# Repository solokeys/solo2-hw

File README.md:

# Solo v2 Hardware

This repo contains the schematic and layout for Solo v2.  Specifically, it contains the Kicad source files
for the "module" PCB which contains all of the relevant circuitry.

What is not included is the "cavity" PCBs, or NFC antenna.

To generate a BOM, see [`bom/`](./bom).

This is only provided as a reference.  If you'd like to submit a PR or otherwise provide feedback, please contact SoloKeys team first.

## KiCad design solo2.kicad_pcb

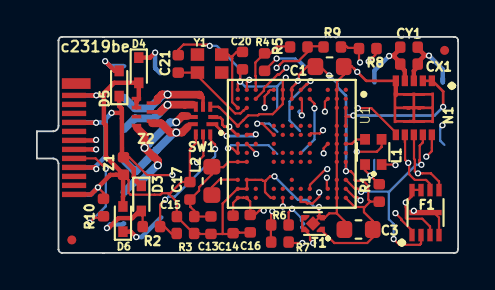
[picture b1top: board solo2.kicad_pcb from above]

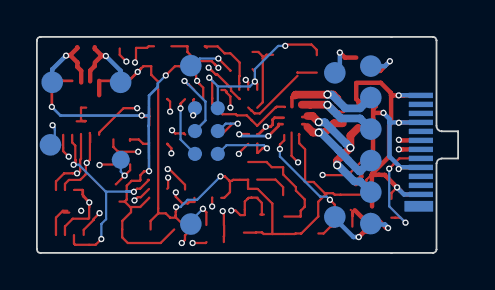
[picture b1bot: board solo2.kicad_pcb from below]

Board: 4 copper layers, 23.4 x 12.0 mm, 41 parts (2 on the bottom side), 43 nets.

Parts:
ABOTTOM_LEFT: Fiducial_0.5mm_Mask1mm
ATOP_RIGHT: Fiducial_0.5mm_Mask1mm
C1, C3: 22u; C_0603_1608Metric
C13, C17: 10uF; C_0402_1005Metric
C14, C15: 100nF; C_0402_1005Metric
C16: 47pF; C_0402_1005Metric
C20, C21: 8pF; C_0402_1005Metric
CX1: DNP; C_0402_1005Metric
CY1: DNP; C_0402_1005Metric
D1: ARM_DEBUG; TC2030-IDC-NL
D3, D4, D5, D6: RB521S30T5G; SOD-523-thin
F1: GD25Q16CEIGR; FLASH_2x3_USON8
L1: LED_RGBA; RGB_LED_606
L2: 4u7H; L_0603_1608Metric
N1: FM11NC08; MLPD3X3
P1: USB_C_Plug; USB-C_WURTH
R1: 180R; R_0402_1005Metric
R2, R10: 5k; R_0402_1005Metric
R3: 40k; R_0402_1005Metric
R4, R6, R8: 10k; R_0402_1005Metric
R5, R7, R9: 500k; R_0402_1005Metric
SW1: FSUSB42
T1: TLV742p; Texas_X2SON-4_1x1mm_P0.65mm
TOP1: TOP_A; top-A
TP1: TestPoint; TestPoint_Pad_D1.0mm
U1: LPC55S69JEV98K; BGA98C50P13X13_700X700X97N
Y1: XRCGB16M000FXN01R0; Crystal-2mmx1.6mm
Z1: GG040205100N2P; R_0402_1005Metric
Z2: PUSB3TB6AZ; XSON7

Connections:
+3V3: C1.1, C3.1, C14.1, C16.1, D1.1, N1.1, N1.2, R1.1, T1.1, U1.A3, U1.A5, U1.A9, U1.A13, U1.G1, U1.G2, U1.M1, U1.M13, U1.N7, U1.N8, U1.N13
/5V: D3.1, D5.1, P1.A4, P1.A9, P1.B4, P1.B9, SW1.9, T1.3, T1.4, Z1.1
/BOT_D+: SW1.5, TOP1.4, Z2.6
/BOT_D-: SW1.4, TOP1.3, Z2.5
/CAP1: R4.1, TOP1.9
/CAP2: R6.1, TOP1.10
/CAP3: R8.1, TOP1.11
/D+: P1.A6, SW1.1, U1.M6
/D-: P1.A7, SW1.2, U1.N6
/NFC+: CX1.1, CY1.1, N1.4, TOP1.12
/NFC-: CX1.2, CY1.2, N1.3, TOP1.13
/SEL: R2.2, R3.2, SW1.10
/TOP_5V: D3.2, R2.1, TOP1.7
/TOP_D+: SW1.7, TOP1.5, Z2.7
/TOP_D-: SW1.6, TOP1.6, Z2.4
/TOP_GND: D4.1, TOP1.1
/solo/FLASH_CS: F1.1, U1.C12
/solo/FLASH_POWER: F1.3, F1.7, F1.8, U1.A12
/solo/Sheet5DDC9C58/B: L1.3, U1.H13
/solo/Sheet5DDC9C58/CHARGE1: R5.2, R7.2, R9.2, U1.C7
/solo/Sheet5DDC9C58/G: L1.2, U1.M7
/solo/Sheet5DDC9C58/NFC_GPIO: N1.10, U1.E6
/solo/Sheet5DDC9C58/R: L1.1, U1.A7
/solo/Sheet5DDC9C58/SENSE1: R4.2, R5.1, U1.L1
/solo/Sheet5DDC9C58/SENSE2: R6.2, R7.1, U1.J1
/solo/Sheet5DDC9C58/SENSE3: R8.2, R9.1, U1.L2
/solo/Sheet5DDC9C58/SPI_CLK: F1.6, N1.7, U1.F13
/solo/Sheet5DDC9C58/SPI_MISO: F1.2, N1.9, U1.A11
/solo/Sheet5DDC9C58/SPI_MOSI: F1.5, N1.8, U1.E12
/solo/Sheet5DDC9C58/SPI_SS: N1.6, U1.C2
/solo/Sheet5DDC9C58/SWCLK: D1.4, U1.F1
/solo/Sheet5DDC9C58/SWDIO: D1.2, U1.E2
/solo/Sheet5DDC9C58/SWO: D1.6, U1.F2
/solo/nRESET: D1.3, U1.J6
GNDREF: C1.2, C3.2, C13.2, C14.2, C15.2, C16.2, C17.2, C20.1, C21.1, D1.5, D4.2, D6.2, F1.4, N1.5, N1.EXP, P1.A1, P1.A12, P1.B1, P1.B12, R3.1, R10.2, SW1.3, SW1.8, T1.2, T1.5, U1.B1, U1.B2, U1.B3, U1.B5, U1.B6, U1.B7, U1.B8, U1.B9, U1.B11, U1.B12, U1.B13, U1.H1, U1.H2, U1.J13, U1.M11, U1.M12, U1.N1, U1.N5, U1.N12, Z1.2, Z2.1, Z2.2
unnamed: C13.1, C15.1, C17.1, L2.2, U1.M9, U1.N9
unnamed: C20.2, U1.N3, Y1.1
unnamed: C21.2, U1.M3, Y1.2
unnamed: D5.2, TOP1.2
unnamed: D6.1, TOP1.8
unnamed: L1.4, R1.2, TP1.1
unnamed: L2.1, U1.N11
unnamed: P1.A5, R10.1

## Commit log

2021-04-26 readme, bom
2021-05-27 add missing schematics and rename
2022-04-18 Add PDF schematic
